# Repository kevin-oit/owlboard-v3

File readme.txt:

This design is based on the Numato Mimas. 

http://numato.com/mimas-spartan-6-fpga-development-board/

Use latest version of Kicad.

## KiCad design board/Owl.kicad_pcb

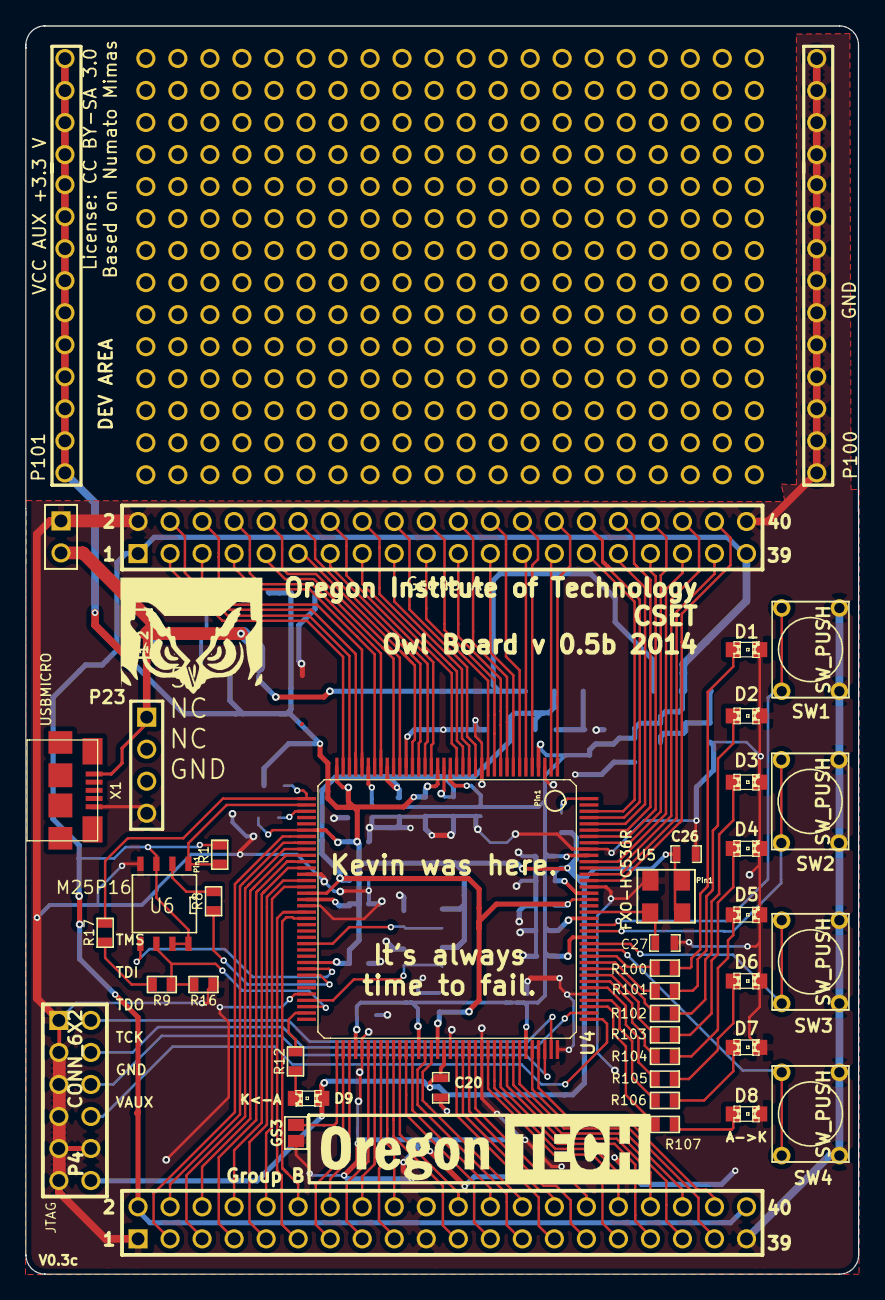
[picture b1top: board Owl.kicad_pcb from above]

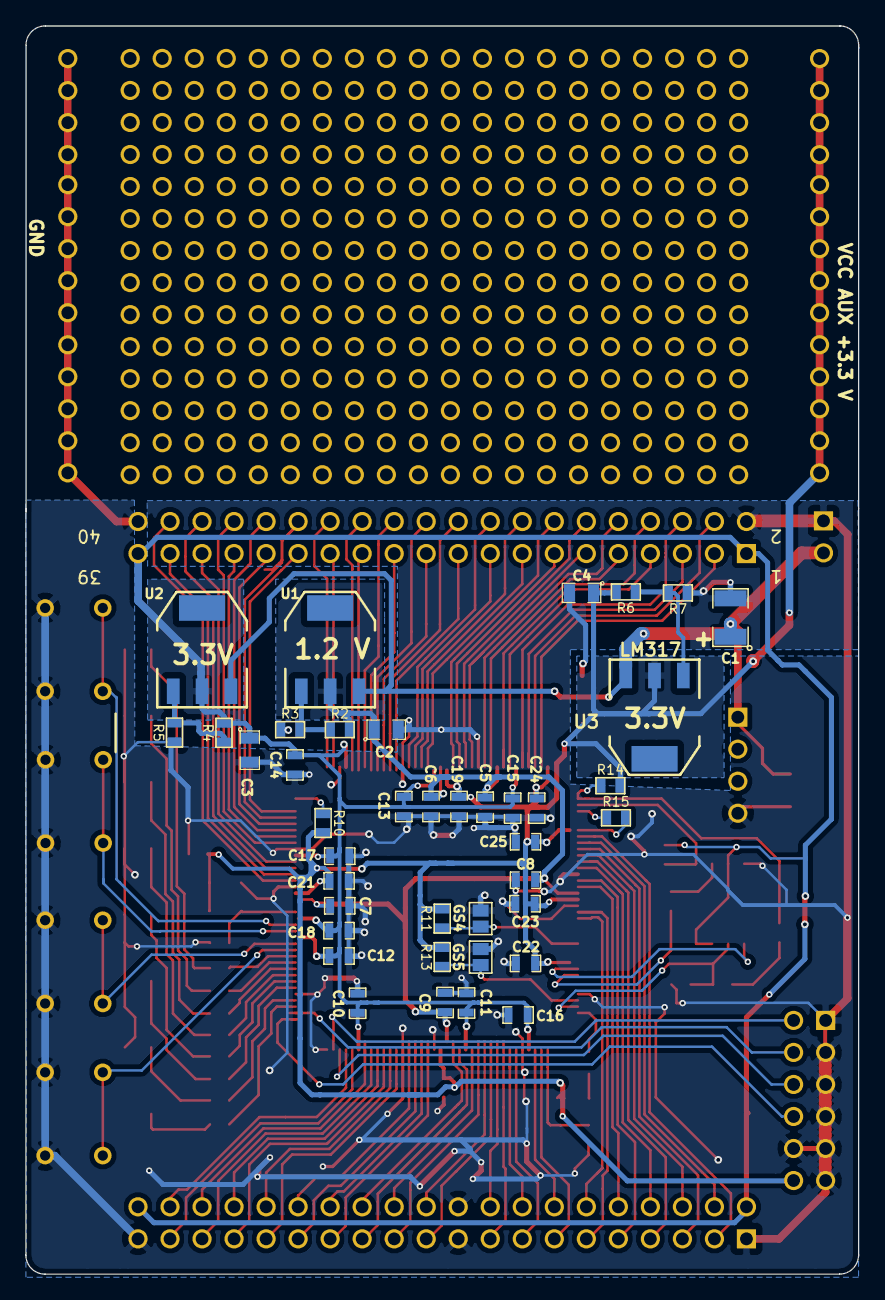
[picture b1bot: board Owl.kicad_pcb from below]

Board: 2 copper layers, 66.1 x 99.0 mm, 82 parts (40 on the bottom side), 117 nets.

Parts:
C1: 47uF; SM1210
C2, C3, C4: 10uF; SM0805
C5, C6, C7, C8, C9, C10, C11, C12, C13, C14, C15, C16, C17, C18, C19, C20, C21, C22, C23, C24, C25, C26: 0.1uF; SM0603_Capa
C27: 15pF; SM0603_Capa
D1, D2, D3, D4, D5, D6, D7, D8, D9: LED; LED-0805
GS3, GS4, GS5: GS2
P1: CONN_2; PIN_ARRAY_2X1
P2, P3: CONN_20X2; PIN_ARRAY_20X2
P4: CONN_6X2; pin_array_6x2
P23: CONN_4; PIN_ARRAY_4x1
P100: GND; pin_array_14x1
P101: VCC AUX +3.3 V; pin_array_14x1
R1, R9, R16: 2.4k; SM0603-ExtraRoom
R2, R3, R4, R5, R6, R7: NC; SM0603-ExtraRoom
R8, R17: 4.7k; SM0603-ExtraRoom
R10, R14, R15: 4.7K; SM0603-ExtraRoom
R11, R13: 10K; SM0603-ExtraRoom
R12: 1K; SM0603-ExtraRoom
R100, R101, R102, R103, R104, R105, R106, R107: 330; SM0603-ExtraRoom
SW1, SW2, SW3, SW4: SW_PUSH; SW_PUSH_FSMJ
U1, U2, U3: LM317; SOT223
U4: XC6SLX9-2TQG144C; TQG144
U5: FXO-HC536R; crystal_FXO-HC53
U6: M25P16; SO8N
X1: USBMICRO; MICRO-B_USB

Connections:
/Gpios/GPIO-N1: P2.3, U4.131
/Gpios/GPIO-N2: P2.5, U4.133
/Gpios/GPIO-N3: P2.7, U4.137
/Gpios/GPIO-N4: P2.9, U4.139
/Gpios/GPIO-N5: P2.11, U4.141
/Gpios/GPIO-N6: P2.13, U4.1
/Gpios/GPIO-N7: P2.15, U4.5
/Gpios/GPIO-N8: P2.17, U4.7
/Gpios/GPIO-N9: P2.19, U4.9
/Gpios/GPIO-N10: P2.21, U4.11
/Gpios/GPIO-N11: P2.23, U4.14
/Gpios/GPIO-N12: P2.25, U4.16
/Gpios/GPIO-N13: P2.27, U4.21
/Gpios/GPIO-N14: P2.29, U4.23
/Gpios/GPIO-N15: P2.31, U4.26
/Gpios/GPIO-N16: P2.33, U4.29
/Gpios/GPIO-N17: P2.35, U4.32
/Gpios/GPIO-N18: P2.37, U4.34
/Gpios/GPIO-N19: P3.30, U4.55
/Gpios/GPIO-N20: P3.6, U4.101
/Gpios/GPIO-N21: P3.4, U4.104
/Gpios/GPIO-N22: P3.32, U4.50
/Gpios/GPIO-N23: P3.38, U4.43
/Gpios/GPIO-N24: P3.34, U4.47
/Gpios/GPIO-N25: P3.36, U4.45
/Gpios/GPIO-N26: P3.28, U4.74
/Gpios/GPIO-N27: P3.26, U4.78
/Gpios/GPIO-N28: P3.24, U4.80
/Gpios/GPIO-N29: P3.20, U4.82
/Gpios/GPIO-N30: P3.18, U4.84
/Gpios/GPIO-N31: P3.16, U4.87
/Gpios/GPIO-N32: P3.14, U4.92
/Gpios/GPIO-N33: P3.12, U4.94
/Gpios/GPIO-N34: P3.10, U4.97
/Gpios/GPIO-N35: P3.8, U4.99
/Gpios/GPIO-P1: P2.4, U4.132
/Gpios/GPIO-P2: P2.6, U4.134
/Gpios/GPIO-P3: P2.8, U4.138
/Gpios/GPIO-P4: P2.10, U4.140
/Gpios/GPIO-P5: P2.12, U4.142
/Gpios/GPIO-P6: P2.14, U4.2
/Gpios/GPIO-P7: P2.16, U4.6
/Gpios/GPIO-P8: P2.18, U4.8
/Gpios/GPIO-P9: P2.20, U4.10
/Gpios/GPIO-P10: P2.22, U4.12
/Gpios/GPIO-P11: P2.24, U4.15
/Gpios/GPIO-P12: P2.26, U4.17
/Gpios/GPIO-P13: P2.28, U4.22
/Gpios/GPIO-P14: P2.30, U4.24
/Gpios/GPIO-P15: P2.32, U4.27
/Gpios/GPIO-P16: P2.34, U4.30
/Gpios/GPIO-P17: P2.36, U4.33
/Gpios/GPIO-P18: P2.38, U4.35
/Gpios/GPIO-P19: P3.29, U4.56
/Gpios/GPIO-P20: P3.5, U4.102
/Gpios/GPIO-P21: P3.3, U4.105
/Gpios/GPIO-P22: P3.31, U4.51
/Gpios/GPIO-P23: P3.37, U4.44
/Gpios/GPIO-P24: P3.33, U4.48
/Gpios/GPIO-P25: P3.35, U4.46
/Gpios/GPIO-P26: P3.27, U4.75
/Gpios/GPIO-P27: P3.25, U4.79
/Gpios/GPIO-P28: P3.23, U4.81
/Gpios/GPIO-P29: P3.19, U4.83
/Gpios/GPIO-P30: P3.17, U4.85
/Gpios/GPIO-P31: P3.15, U4.88
/Gpios/GPIO-P32: P3.13, U4.93
/Gpios/GPIO-P33: P3.11, U4.95
/Gpios/GPIO-P34: P3.9, U4.98
/Gpios/GPIO-P35: P3.7, U4.100
/Gpios/LED0: R100.1, U4.119
/Gpios/LED1: R101.1, U4.118
/Gpios/LED2: R102.1, U4.117
/Gpios/LED3: R103.1, U4.116
/Gpios/LED4: R104.1, U4.115
/Gpios/LED5: R105.1, U4.114
/Gpios/LED6: R106.1, U4.112
/Gpios/LED7: R107.1, U4.111
/Gpios/SW0: SW1.1, U4.124
/Gpios/SW1: SW2.1, U4.123
/Gpios/SW2: SW3.1, U4.121
/Gpios/SW3: SW4.1, U4.120
/Gpios/VCCIO: C3.1, C10.1, C11.1, C12.1, C13.1, C14.1, C15.1, C16.1, C17.1, C18.1, P2.2, P2.40, P3.1, P3.39, R1.1, R4.1, U2.2, U4.4, U4.18, U4.31, U4.76, U4.86, U4.103, U4.122, U4.125, U4.135, U6.3, U6.7, U6.8
/PowerSupply/VCCAUX: C4.1, C19.1, C20.1, C21.1, C22.1, C23.1, C24.1, C25.1, C26.1, D9.1, P4.12, P101.1, P101.2, P101.3, P101.4, P101.5, P101.6, P101.7, P101.8, P101.9, P101.10, P101.11, P101.12, P101.13, P101.14, R6.1, R10.1, R11.1, R13.1, R14.1, R15.1, U3.2, U4.20, U4.36, U4.42, U4.53, U4.63, U4.90, U4.129, U5.1, U5.4
/PowerSupply/VCCIN: C1.1, P1.2, P23.1, U1.3, U2.3, U3.3, X1.1
/PowerSupply/VCCINT: C2.1, C5.1, C6.1, C7.1, C8.1, C9.1, R2.1, U1.2, U4.19, U4.28, U4.52, U4.89, U4.128
/XC6SLX9/CCLK: R9.2, R16.1, U4.70, U6.6
/XC6SLX9/CSO_B: R1.2, U4.38, U6.1
/XC6SLX9/DIN: R8.2, U4.65
/XC6SLX9/DONE: R12.1, U4.71
/XC6SLX9/GCLK: C27.1, U4.126, U5.3
/XC6SLX9/HSWAP: R10.2, U4.144
/XC6SLX9/INIT_B: R15.2, U4.39
/XC6SLX9/M0: GS5.1, R13.2, U4.69
/XC6SLX9/M1: GS4.1, R11.2, U4.60
/XC6SLX9/MOSI: U4.64, U6.5
/XC6SLX9/PROGB: R14.2, R17.1, U4.37
/XC6SLX9/SUSPEND: GS3.1, U4.73
GND: C1.2, C2.2, C3.2, C4.2, C5.2, C6.2, C7.2, C8.2, C9.2, C10.2, C11.2, C12.2, C13.2, C14.2, C15.2, C16.2, C17.2, C18.2, C19.2, C20.2, C21.2, C22.2, C23.2, C24.2, C25.2, C26.2, C27.2, D1.2, D2.2, D3.2, D4.2, D5.2, D6.2, D7.2, D8.2, GS3.2, GS4.2, GS5.2, P1.1, P2.1, P2.39, P3.2, P3.21, P3.22, P3.40, P4.1, P4.3, P4.5, P4.7, P4.9, P4.10, P4.11, P23.4, P100.1, P100.2, P100.3, P100.4, P100.5, P100.6, P100.7, P100.8, P100.9, P100.10, P100.11, P100.12, P100.13, P100.14, R3.2, R5.2, R7.2, R16.2, SW1.2, SW2.2, SW3.2, SW4.2, U4.3, U4.13, U4.25, U4.49, U4.54, U4.68, U4.77, U4.91, U4.96, U4.108, U4.113, U4.130, U4.136, U5.2, U6.4, X1.5
unnamed: R9.1, R17.2
unnamed: R8.1, U6.2
unnamed: R2.2, R3.1, U1.1
unnamed: R4.2, R5.1, U2.1
unnamed: R6.2, R7.1, U3.1
unnamed: D9.2, R12.2
unnamed: D1.1, R100.2
unnamed: D8.1, R107.2
unnamed: D3.1, R102.2
unnamed: D4.1, R103.2
unnamed: D5.1, R104.2
unnamed: D7.1, R106.2
unnamed: D2.1, R101.2
unnamed: D6.1, R105.2
TCK: P4.8, U4.109
TDI: P4.4, U4.110
TDO: P4.6, U4.106
TMS: P4.2, U4.107

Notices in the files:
board/Owl.kicad_pcb:
License: CC BY-SA 3.0
